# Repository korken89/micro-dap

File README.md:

# Micro CMSIS-DAP Probe (µDAP)

A small [CMSIS-DAP](https://arm-software.github.io/CMSIS_5/DAP/html/index.html) probe, based on the pinout of the [dap42 firmware](https://github.com/devanlai/dap42).

## Changes

### v1.0

* First release

## Resources

### Schematics

TODO

### Programming instructions

The first time you connect the probe (if it has not been flashed yet) it will come up in DFU bootloader mode, and the following instructions will flash the probe:

```console
# Clone and build the firmware
git clone --recursive https://github.com/devanlai/dap42.git
cd dap42
make

# Flash the probe
cd build
dfu-util -d 1209:da42,0483:df11  -a 0 -s 0x08000000:leave -D DAP42.bin
```

Which should give the following output:

```console
# ....

DFU mode device DFU version 011a
Device returned transfer size 2048
DfuSe interface name: "Internal Flash  "
Downloading to address = 0x08000000, size = 15764
Download	[=========================] 100%        15764 bytes
Download done.
File downloaded successfully
Transitioning to dfuMANIFEST state
```

Now the probe is ready to use with `OpenOCD` using the following config file for `nrf52`, but you can replace it with any supported target:

```
# openocd_dap.cfg

source [find interface/cmsis-dap.cfg]
transport select swd
source [find target/nrf52.cfg]
```

### Usage

Using the previous config:

```console
openocd -f openocd_dap.cfg
```

Should give an output similar to:

```console
Open On-Chip Debugger 0.10.0+dev-00924-g16496488d (2019-08-18-15:42)
Licensed under GNU GPL v2
For bug reports, read
	http://openocd.org/doc/doxygen/bugs.html
Info : Listening on port 6666 for tcl connections
Info : Listening on port 4444 for telnet connections
Info : CMSIS-DAP: SWD  Supported
Info : CMSIS-DAP: FW Version = 1.0
Info : CMSIS-DAP: Interface Initialised (SWD)
Info : SWCLK/TCK = 1 SWDIO/TMS = 1 TDI = 0 TDO = 0 nTRST = 0 nRESET = 0
Info : CMSIS-DAP: Interface ready
Info : clock speed 1000 kHz
Info : SWD DPIDR 0x2ba01477
Info : nrf52.cpu: hardware has 6 breakpoints, 4 watchpoints
Info : nrf52.cpu: external reset detected
Info : Listening on port 3333 for gdb connections
```

### Images

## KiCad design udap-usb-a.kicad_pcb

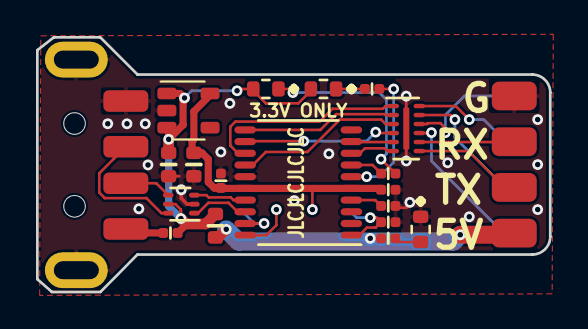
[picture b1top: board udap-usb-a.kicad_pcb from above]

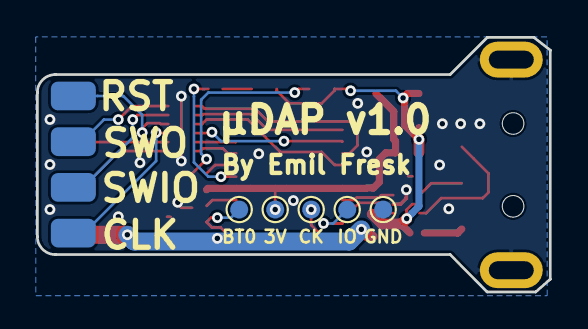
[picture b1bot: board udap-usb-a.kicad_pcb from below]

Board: 2 copper layers, 28.5 x 14.1 mm, 25 parts (5 on the bottom side), 30 nets.

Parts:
C1, C3, C4: 100n; C_0402
C2, C5: 4.7u; C_0603
D1, D2, D201: LTST-C191KGKT; LEDC1608X60
F1: MF-FSMF050X-2; R_0603
FB101: Ferrite_Bead_Small; R_0402
J201: Conn_02x04_Counter_Clockwise; 2x4_2.54mm_side
P101: USB_A; USB_A_1001-011-01101
R1, R2, R202: 470; R_0402
R201: 5.1k; R_0402
TP1, TP2, TP3, TP201, TP202: Test_Point; TestPoint_Pad_D1.0mm
U2: MIC5245-3.3YM5; SOT-23-5
U4: NUF2042XV6T1G; DFN-6-1EP_1.2x1.6mm_P0.5mm
U201: NUF6401MNT1; DFN-12-1EP_1.35x3mm_P0.5mm
U202: STM32F042F6Px; TSSOP-20_4.4x6.5mm_P0.65mm

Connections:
+3V3: C3.1, C4.1, C5.1, TP201.1, U2.5, U202.5, U202.16
+5V: C2.1, D1.2, D201.2, F1.2, FB101.1, U2.1, U2.3, U4.5
/DM: P101.2, U4.4
/DP: P101.3, U4.6
/core/BOOT0: R201.1, TP202.1, U202.1
/core/DM_P: U4.3, U202.17
/core/DP_P: U4.1, U202.18
/core/LED0: R1.1, U202.6
/core/LED1: R202.1, U202.7
/core/NRST: C1.2, U202.4
/core/SWCLK: TP2.1, U202.20
/core/SWDIO: TP1.1, U202.19
/core/TGT_RST: U201.3, U202.14
/core/TGT_RSTo: J201.8, U201.10
/core/TGT_RX: U201.6, U202.8
/core/TGT_RXo: J201.2, U201.7
/core/TGT_SWCLK: U201.4, U202.12
/core/TGT_SWCLKo: J201.5, U201.9
/core/TGT_SWDIO: U201.2, U202.11
/core/TGT_SWDIOo: J201.6, U201.11
/core/TGT_SWO: U201.1, U202.13
/core/TGT_SWOo: J201.7, U201.12
/core/TGT_TX: U201.5, U202.9
/core/TGT_TXo: J201.3, U201.8
GND: C1.1, C2.2, C3.2, C4.2, C5.2, D2.1, J201.4, P101.4, P101.5, R201.2, TP3.1, U2.2, U4.2, U201.13, U202.15
unnamed: D1.1, R1.2
unnamed: D2.2, R2.2
unnamed: D201.1, R202.2
unnamed: F1.1, J201.1, R2.1
unnamed: FB101.2, P101.1

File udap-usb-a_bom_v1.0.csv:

Reference, Value, Footprint, Datasheet, MFPN
"P101","USB_A","usb:USB_A_1001-011-01101","","1001-011-01101"
"C4","100n","passive:C_0402","~"
"C3","100n","passive:C_0402","~"
"U2","MIC5245-3.3YM5","sot:SOT-23-5","http://ww1.microchip.com/downloads/en/devicedoc/mic5205.pdf"
"C2","4.7u","passive:C_0603","~"
"C5","4.7u","passive:C_0603","~"
"R1","470","passive:R_0402","~"
"F1","MF-FSMF050X-2","passive:R_0603","http://www.bourns.com/docs/Product-Datasheets/mffsmf.pdf"
"C1","100n","passive:C_0402","~"
"U4","NUF2042XV6T1G","dfn:DFN-6-1EP_1.2x1.6mm_P0.5mm","http://www.onsemi.com/pub/Collateral/NUF2030XV6-D.PDF"
"D2","LTST-C191KGKT","leds:LEDC1608X60","~"
"R2","470","passive:R_0402","~"
"U202","STM32F042F6Px","sop:TSSOP-20_4.4x6.5mm_P0.65mm","http://www.st.com/st-web-ui/static/active/en/resource/techni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"
"D201","LTST-C191KGKT","leds:LEDC1608X60","~"
"R202","470","passive:R_0402","~"
"R201","5.1k","passive:R_0402","~"
"U201","NUF6401MNT1","dfn:DFN-12-1EP_1.35x3mm_P0.5mm","https://www.onsemi.cn/pub/Collateral/NUF6401-D.PDF"
"J201","2x4 pin header","connectors:2x4_2.54mm_side","~"
"D1","LTST-C191KGKT","leds:LEDC1608X60","~"

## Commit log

2019-08-13 Minor fix
2019-08-13 Added render
2019-08-19 USB-A version
2019-08-22 Update text and links from µBMP to µDAP
2019-08-22 Rotate D2 to move its silk screen in-bounds
2019-08-22 Fix BT0 test-point traces
2019-08-23 Move the testpoints towards the USB connector
2019-08-23 Amend schematic for USB-A version
2019-08-23 Update PCB for USB-A version
2019-08-23 Rename files to indicate USB-A version
2019-08-23 Rename files to indicate USB-C version
2019-09-11 Added BOM
2019-09-12 Spaced 4.7u apart more, now easier to solder
2019-09-20 Fixed bom error
2019-09-20 Added flashing instructions
2019-09-20 Add JLCPCB Order Number placeholder
    This adds silkscreen under the MCU saying "JLCJLCJLCJLC". When ordering
    with JLCPCB, they'll replace this with the order number. If this isn't
    done, the order number will be placed somewhere random where it can
    potentially be seen after assembly.
    Since this is purely for a slight convenience when using JLCPCB, I can
    also see just not doing this.
2019-09-20 Fix datasheet URL for the regulator
    It used to link to a different regulator that could supply much less
    current
2019-09-25 Swap TX and RX on silkscreen
2019-09-25 Also fix USB-A version
2019-09-26 Added ferrite bead on 5V, PC EMI -> TARGET issue mitigation
